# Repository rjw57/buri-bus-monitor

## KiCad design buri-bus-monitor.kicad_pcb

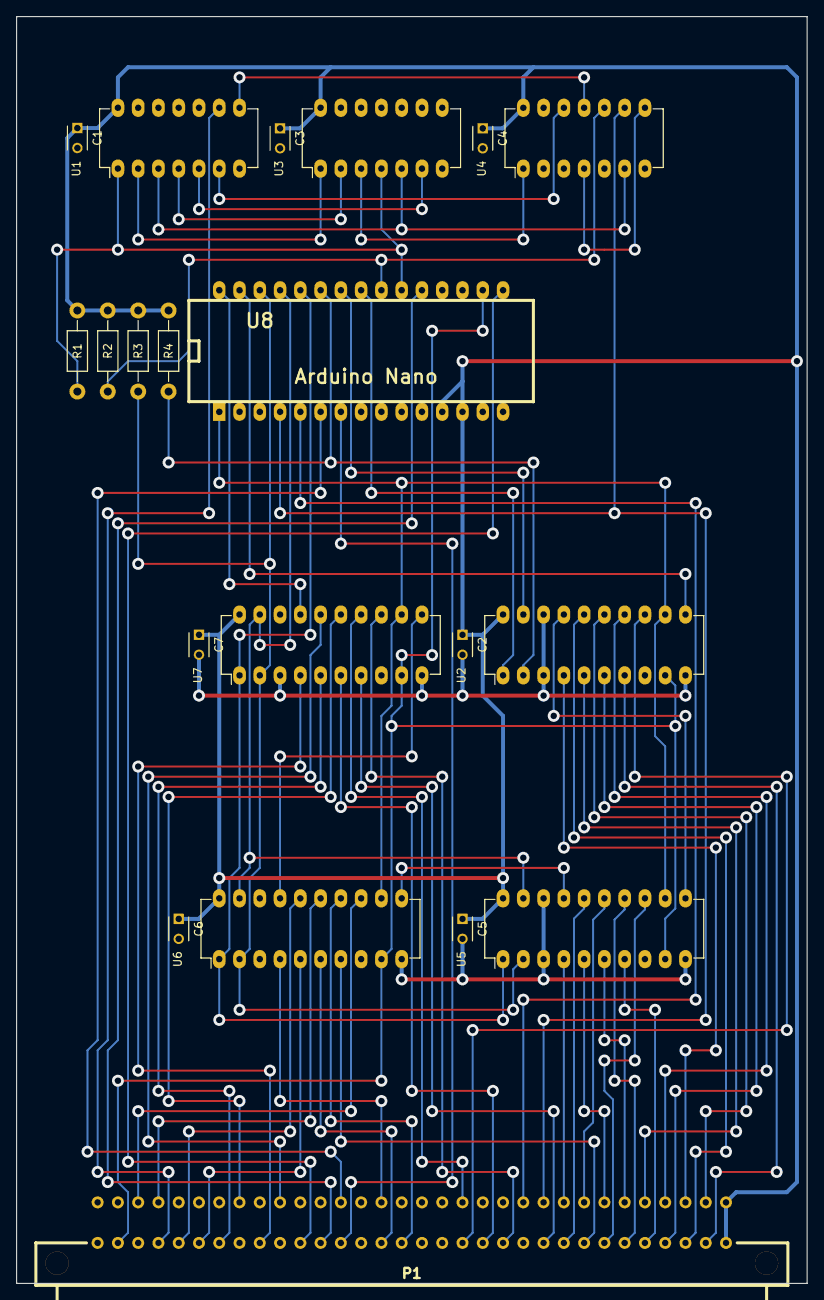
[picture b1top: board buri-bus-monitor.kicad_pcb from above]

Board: 2 copper layers, 99.1 x 158.8 mm, 20 parts (0 on the bottom side), 64 nets.

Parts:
C1, C2, C3, C4, C5, C6, C7: 100n; C_Disc_D3_P2.5
P1: Buri-Bus; buri-bus-male
R1, R2, R3, R4: 3K3; Resistor_Horizontal_RM10mm
U1: 74HC04; DIP-14_W7.62mm_LongPads
U2, U5, U6, U7: 74LS299; DIP-20_W7.62mm_LongPads
U3: 74HC00; DIP-14_W7.62mm_LongPads
U4: 74HC74; DIP-14_W7.62mm_LongPads
U8: Arduino Nano; arduino_mini

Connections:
+5V: C1.1, C2.1, C3.1, C4.1, C5.1, C6.1, C7.1, P1.1a, P1.1c, R1.2, R2.2, R3.2, R4.2, U1.14, U2.20, U3.14, U4.13, U4.14, U5.20, U6.20, U7.20, U8.12, U8.13
/A0: P1.5c, U5.7
/A1: P1.7c, U5.13
/A2: P1.6a, U5.6
/A3: P1.6c, U5.14
/A4: P1.7a, U5.5
/A5: P1.8a, U5.15
/A6: P1.9a, U5.4
/A7: P1.9c, U5.16
/A8: P1.8c, U6.7
/A9: P1.30a, U6.13
/A10: P1.18c, U6.6
/A11: P1.17c, U6.14
/A12: P1.27c, U6.5
/A13: P1.29a, U6.15
/A14: P1.18a, U6.4
/A15: P1.28c, U6.16
/A16: P1.10c, U7.7
/A17: P1.12c, U7.13
/A18: P1.13c, U7.6
/A19: P1.14a, U7.14
/A20: P1.26c, U7.5
/A21: P1.25a, U7.15
/A22: P1.24c, U7.4
/A23: P1.23a, U7.16
/AS0: U5.1, U6.1, U7.1, U8.26
/AS1: U5.19, U6.19, U7.19, U8.27
/BE: P1.11a, U8.5
/D0: P1.2c, U2.7
/D1: P1.14c, U2.13
/D2: P1.4c, U2.6
/D3: P1.4a, U2.14
/D4: P1.5a, U2.5
/D5: P1.2a, U2.15
/D6: P1.3a, U2.4
/D7: P1.3c, U2.16
/DS0: U2.1, U8.23
/DS1: U2.19, U8.24
/HALT: R2.1, U4.10, U8.22
/MISO: U7.17, U8.30
/MOSI: U2.11, U8.29
/PHI2: P1.29c, U1.9
/RDY: P1.10a, U4.9, U8.4
/R~W: P1.22c, U8.16
/SCLK: U2.12, U5.12, U6.12, U7.12, U8.1
/STEP: R1.1, U1.1, U3.4, U8.21
/SYNC: P1.20a, U8.6
/~AOE: R3.1, U5.2, U6.2, U7.2, U8.28
/~DOE: R4.1, U2.2, U8.25
/~IRQ: P1.21c, U8.20
/~NMI: P1.20c, U8.7
/~RST: P1.31c, U2.9, U5.9, U6.9, U7.9, U8.17
GND: C1.2, C2.2, C3.2, C4.2, C5.2, C6.2, C7.2, P1.32a, P1.32c, U1.7, U2.3, U2.10, U2.18, U3.7, U4.2, U4.3, U4.7, U5.3, U5.10, U5.18, U6.3, U6.10, U6.18, U7.3, U7.10, U7.18, U8.14, U8.19
unnamed: U1.2, U3.1
unnamed: U1.3, U3.5, U4.6
unnamed: U1.4, U3.2
unnamed: U1.5, U3.6
unnamed: U1.6, U4.12
unnamed: U1.8, U4.11
unnamed: U2.17, U5.11
unnamed: U3.3, U4.1
unnamed: U4.4, U4.8
unnamed: U5.17, U6.11
unnamed: U6.17, U7.11

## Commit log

2015-03-02 Add 'hardware/' from commit 'bca2b16177ccbec92d3bf39c45d46f6bc6f2190b'
    git-subtree-dir: hardware
    git-subtree-mainline: 3b3902222f55224fbe4e8fc56c0c1c6d8ff289fa
    git-subtree-split: bca2b16177ccbec92d3bf39c45d46f6bc6f2190b
2015-03-02 upload_helper: Py3 compatibility
2016-01-09 first version
2016-01-09 first pass at layout
2016-01-09 add plots
2016-01-09 regenerate ground fill
2016-01-09 correct single step logic
2016-01-11 Add input for non data/address bus
2016-01-11 Update LSB first shift regs
2016-01-11 move display control to SDA/SCK pins
2016-01-11 rearrange pins on Arduino
2016-01-11 Make firmware compatible with Arduino IDE
2016-01-12 add Makefile using Arduino IDE CLI
2016-01-12 add first draft of front panel layout
2016-01-12 Convert display to SPI
2016-01-12 Re-order bus pins on '165 to match current hardware
2016-01-12 Coalesce AS0 and DS0 lines
2016-01-13 wire up bus signal control lines
2016-01-13 Add notes on SPI protocol for bus
2016-01-13 Fix markdown syntax for SPI protocol
2016-01-13 Add note on when sampling happens
2016-01-13 tart up front panel a little
2016-01-13 recenter front panel artwork
2016-01-13 resize front panel to Poundland whiteboards
2016-01-13 resize front panel to Poundland whiteboards better
2016-01-13 Add negation symbol to signals
2016-01-13 updae front panel with lessons from prototype 1
2016-01-14 Latest revision of front panel
2016-01-24 update SPI bus monitor interface to be MSB first
2016-01-26 add HALT and RESET support
2016-01-26 add basic editorconfig
2016-01-26 implement cycle and instruction step
2016-01-26 enable dposit and deposit next features
2016-08-07 add dumb firmware
